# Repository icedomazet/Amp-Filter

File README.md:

Files for RCJ should be put in directory C:/Program Files/KiCad/9.0(or whatever version you have)/share/kicad then in 3dmodels are .step, symbols are .sym, and footprints are .mod

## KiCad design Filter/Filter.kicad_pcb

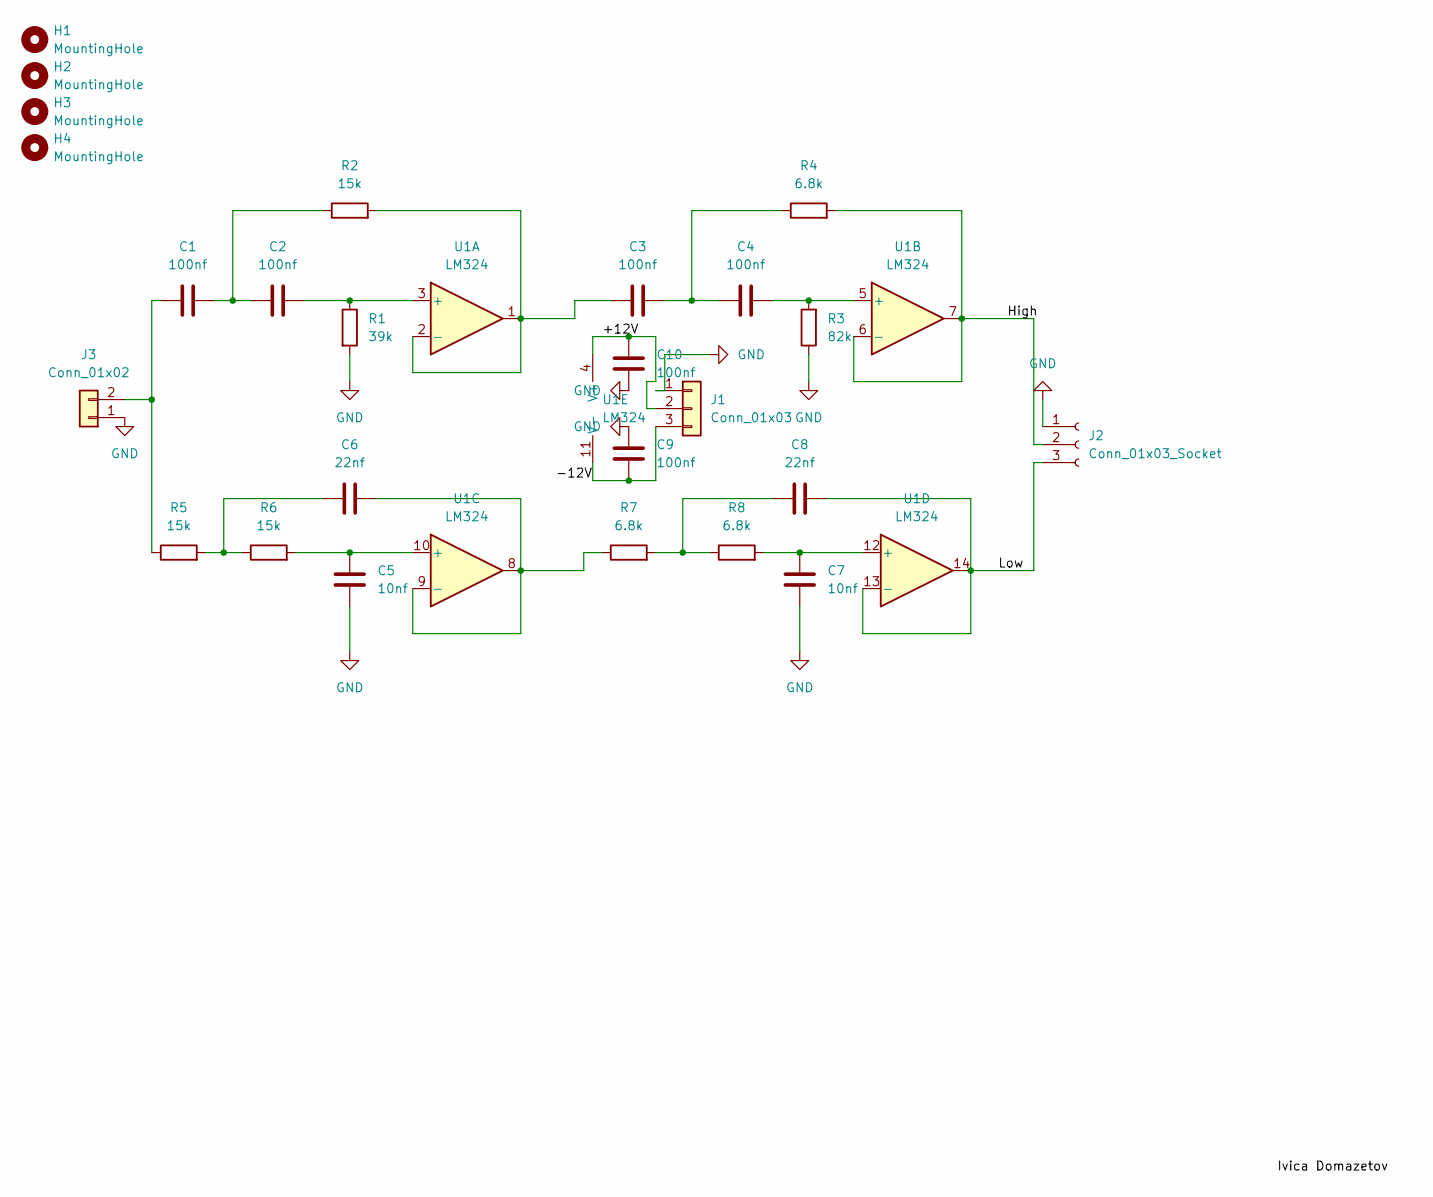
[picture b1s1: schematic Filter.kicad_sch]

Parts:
C1, C2, C3, C4, C9, C10: 100nf; C_Disc_D5.0mm_W2.5mm_P2.50mm
C5, C7: 10nf; C_Disc_D5.0mm_W2.5mm_P2.50mm
C6, C8: 22nf; C_Disc_D5.0mm_W2.5mm_P2.50mm
H1, H2, H3, H4: MountingHole; MountingHole_2.7mm_M2.5_ISO14580
J1: Conn_01x03; TerminalBlock_MaiXu_MX126-5.0-03P_1x03_P5.00mm
J2: Conn_01x03_Socket; SAMESKY_RCJ-2221
J3: Conn_01x02; SAMESKY_RCJ-042
R1: 39k; R_Axial_DIN0207_L6.3mm_D2.5mm_P10.16mm_Horizontal
R2, R5, R6: 15k; R_Axial_DIN0207_L6.3mm_D2.5mm_P10.16mm_Horizontal
R3: 82k; R_Axial_DIN0207_L6.3mm_D2.5mm_P10.16mm_Horizontal
R4, R7, R8: 6.8k; R_Axial_DIN0207_L6.3mm_D2.5mm_P10.16mm_Horizontal
U1: LM324; DIP-14_W7.62mm_LongPads

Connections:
/+12V: C10.2, J1.2, U1.4 (V+)
/-12V: C9.1, J1.3, U1.11 (V-)
/High: J2.2, R4.2, U1.6 (-), U1.7
/Low: C8.1, J2.3, U1.13 (-), U1.14
GND: C5.1, C7.1, C9.2, C10.1, J1.1, J2.1, J3.1, R1.2, R3.1
unnamed: C1.2, C2.1, R2.1
unnamed: C3.2, C4.1, R4.1
unnamed: C6.2, R5.2, R6.1
unnamed: C8.2, R7.2, R8.1
unnamed: C1.1, J3.2, R5.1
unnamed: C2.2, R1.1, U1.3 (+)
unnamed: C3.1, R2.2, U1.1, U1.2 (-)
unnamed: C4.2, R3.2, U1.5 (+)
unnamed: C5.2, R6.2, U1.10 (+)
unnamed: C6.1, R7.1, U1.8, U1.9 (-)
unnamed: C7.2, R8.2, U1.12 (+)

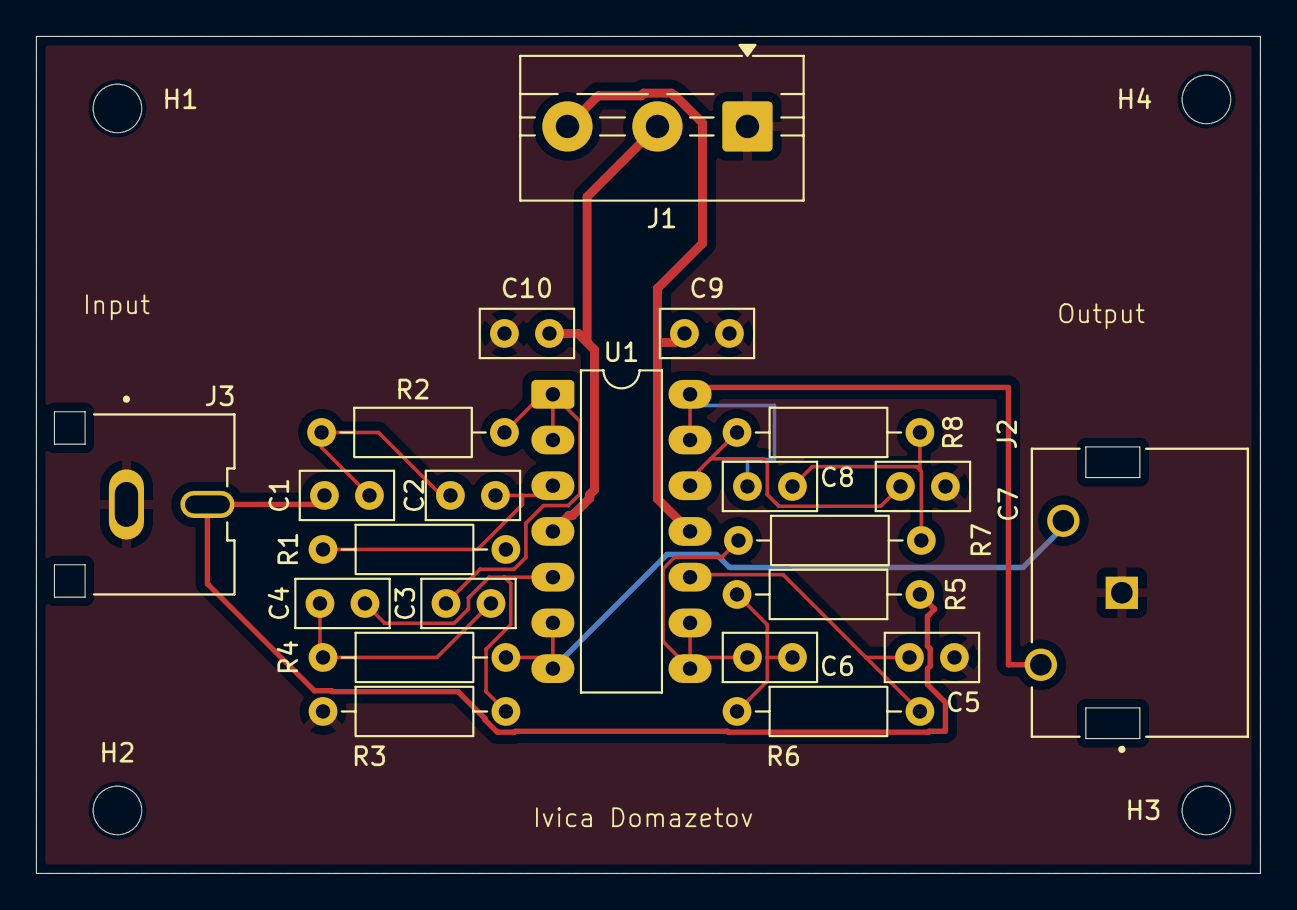
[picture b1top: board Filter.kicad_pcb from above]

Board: 2 copper layers, 68.0 x 46.5 mm, 26 parts (0 on the bottom side), 16 nets.
